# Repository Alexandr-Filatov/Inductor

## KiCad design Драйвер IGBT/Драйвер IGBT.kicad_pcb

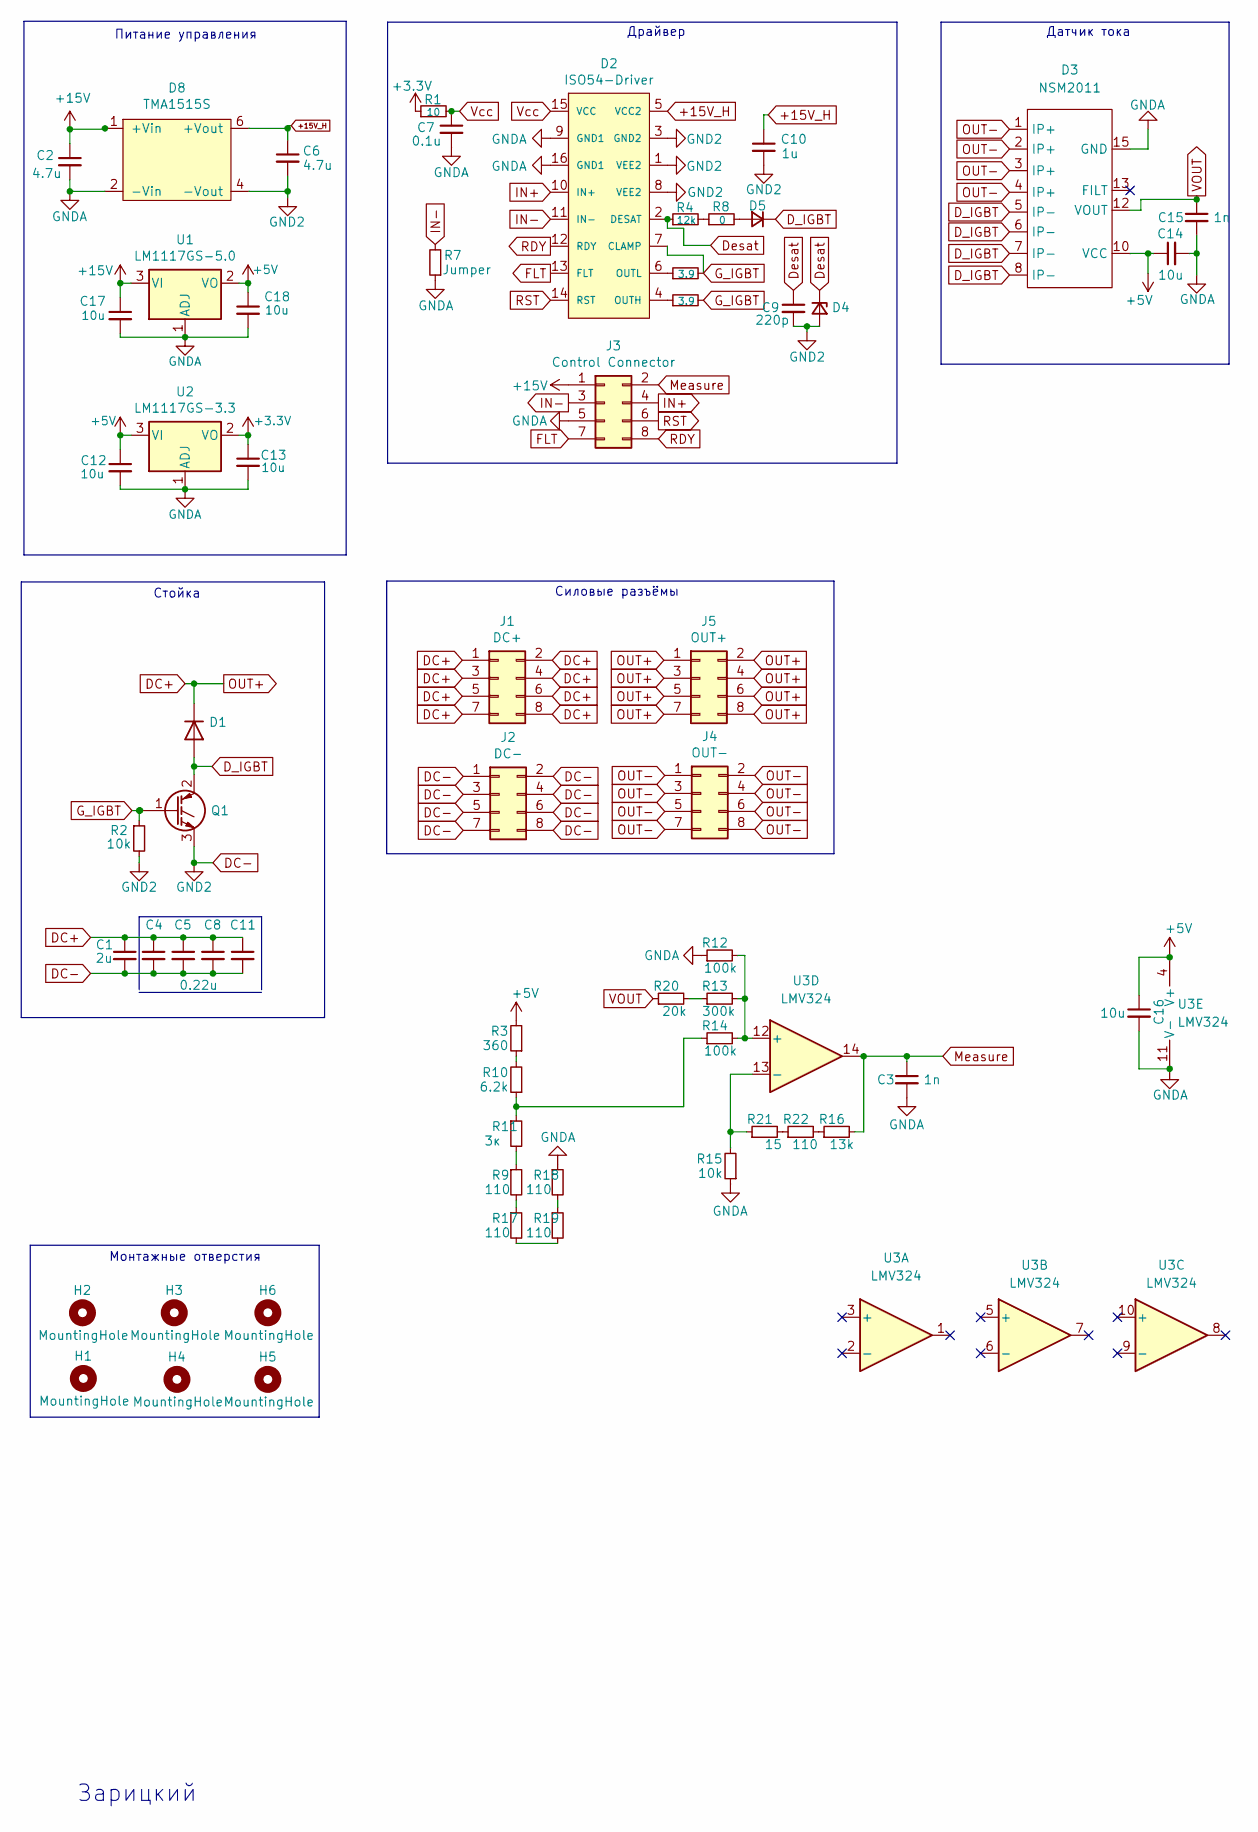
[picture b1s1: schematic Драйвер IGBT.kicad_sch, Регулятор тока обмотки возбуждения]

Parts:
C1: 2u; C_Rect_L31.5mm_W13.0mm_P27.50mm_MKS4
C2, C6: 4.7u; C_1210_3225Metric_Pad1.42x2.65mm_HandSolder
C3, C15: 1n; C_0805_2012Metric_Pad1.18x1.45mm_HandSolder
C4, C5, C8, C11: 0.22u; C_2220_5650Metric_Pad1.97x5.40mm_HandSolder
C7: 0.1u; C_0603_1608Metric_Pad1.05x0.95mm_HandSolder
C9: 220p; C_0603_1608Metric_Pad1.05x0.95mm_HandSolder
C10: 1u; C_0603_1608Metric_Pad1.05x0.95mm_HandSolder
C12, C13, C17, C18: 10u; C_0805_2012Metric_Pad1.15x1.40mm_HandSolder
C14, C16: 10u; C_0805_2012Metric_Pad1.18x1.45mm_HandSolder
D1: VS-60EPF06-M3; TO-247-2_Vertical
D2: ISO54-Driver; SOIC-16W_7.5x10.3mm_P1.27mm
D3: NSM2011; SOIC-16W_7.5x10.3mm_P1.27mm
D4: BZT52C10-7-F; D_SOD-123
D5: MURS360T3G; D_SMC
D8: TMA1515S
H1, H2, H3, H4, H5, H6: MountingHole; MountingHole_3mm
J1: DC+; Molex_Micro-Fit_3.0_43045-0800_2x04_P3.00mm_Horizontal
J2: DC-; Molex_Micro-Fit_3.0_43045-0800_2x04_P3.00mm_Horizontal
J3: Control Connector; Molex_Micro-Fit_3.0_43045-0800_2x04_P3.00mm_Horizontal
J4: OUT-; Molex_Micro-Fit_3.0_43045-0800_2x04_P3.00mm_Horizontal
J5: OUT+; Molex_Micro-Fit_3.0_43045-0800_2x04_P3.00mm_Horizontal
Q1: HGTG20N60A4; TO-247-3_Vertical
R1: 10; R_0805_2012Metric_Pad1.15x1.40mm_HandSolder
R2: 10k; R_0805_2012Metric_Pad1.15x1.40mm_HandSolder
R3: 360; R_0805_2012Metric_Pad1.20x1.40mm_HandSolder
R4: 12k; R_0805_2012Metric_Pad1.15x1.40mm_HandSolder
R5, R6: 3.9; R_1206_3216Metric_Pad1.42x1.75mm_HandSolder
R7: Jumper; R_0805_2012Metric_Pad1.15x1.40mm_HandSolder
R8: 0; D_SOD-123
R9, R17, R18, R19, R22: 110; R_0805_2012Metric_Pad1.20x1.40mm_HandSolder
R10: 6.2k; R_0805_2012Metric_Pad1.20x1.40mm_HandSolder
R11: 3к; R_0805_2012Metric_Pad1.20x1.40mm_HandSolder
R12, R14: 100k; R_0805_2012Metric_Pad1.20x1.40mm_HandSolder
R13: 300k; R_0805_2012Metric_Pad1.20x1.40mm_HandSolder
R15: 10k; R_0805_2012Metric_Pad1.20x1.40mm_HandSolder
R16: 13k; R_0805_2012Metric_Pad1.20x1.40mm_HandSolder
R20: 20k; R_0805_2012Metric_Pad1.20x1.40mm_HandSolder
R21: 15; R_0805_2012Metric_Pad1.20x1.40mm_HandSolder
U1: LM1117GS-5.0; SOT-223
U2: LM1117GS-3.3; SOT-223
U3: LMV324

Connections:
+3V3: C13.1, R1.1, U2.2 (VO)
+5V: C12.1, C14.1, C16.1, C18.1, D3.10 (VCC), R3.2, U1.2 (VO), U2.3 (VI), U3.4 (V+)
+15V: C2.1, C17.1, D8.1 (+Vin), J3.1, U1.3 (VI)
+15V_H: C6.1, C10.1, D2.5 (VCC2), D8.6 (+Vout)
DC+: C1.1, C4.1, C5.1, C8.1, C11.1, D1.1 (K), J1.1, J1.2, J1.3, J1.4, J1.5, J1.6, J1.7, J1.8, J5.1, J5.2, J5.3, J5.4, J5.5, J5.6, J5.7, J5.8
DC-: C1.2, C4.2, C5.2, C6.2, C8.2, C9.2, C10.2, C11.2, D2.1 (VEE2), D2.3 (GND2), D2.8 (VEE2), D4.2 (A), D8.4 (-Vout), J2.1, J2.2, J2.3, J2.4, J2.5, J2.6, J2.7, J2.8, Q1.3 (E), R2.2
D_IGBT: D1.2 (A), D3.5 (IP-), D3.6 (IP-), D3.7 (IP-), D3.8 (IP-), D5.1 (K), Q1.2 (C)
Desat: C9.1, D2.2 (DESAT), D4.1 (K), R4.1
FLT: D2.13 (FLT), J3.7
GNDA: C2.2, C3.2, C7.2, C12.2, C13.2, C14.2, C15.2, C16.2, C17.2, C18.2, D2.9 (GND1), D2.16 (GND1), D3.15 (GND), D8.2 (-Vin), J3.5, R7.1, R12.1, R15.1, R18.1, U1.1 (ADJ), U2.1 (ADJ), U3.11 (V-)
G_IGBT: D2.7 (CLAMP), Q1.1 (G), R2.1, R5.2, R6.2
IN+: D2.10 (IN+), J3.4
IN-: D2.11 (IN-), J3.3, R7.2
Measure: C3.1, J3.2, R16.2, U3.14
unnamed: D2.4 (OUTH), R6.1
unnamed: D2.6 (OUTL), R5.1
unnamed: D5.2 (A), R8.2
unnamed: R4.2, R8.1
unnamed: R3.1, R10.2
unnamed: R9.1, R11.2
unnamed: R12.2, R13.2, R14.2, U3.12 (+)
unnamed: R13.1, R20.2
unnamed: R10.1, R11.1, R14.1
unnamed: R15.2, R21.1, U3.13 (-)
unnamed: R16.1, R22.2
unnamed: R9.2, R17.1
unnamed: R17.2, R19.2
unnamed: R18.2, R19.1
unnamed: R21.2, R22.1
OUT-: D3.1 (IP+), D3.2 (IP+), D3.3 (IP+), D3.4 (IP+), J4.1, J4.2, J4.3, J4.4, J4.5, J4.6, J4.7, J4.8
RDY: D2.12 (RDY), J3.8
RST: D2.14 (RST), J3.6
VOUT: C15.1, D3.12 (VOUT), R20.1
Vcc: C7.1, D2.15 (VCC), R1.2

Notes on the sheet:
Драйвер
Зарицкий
Питание управления
Силовые разъёмы
Стойка
Монтажные отверстия
Датчик тока

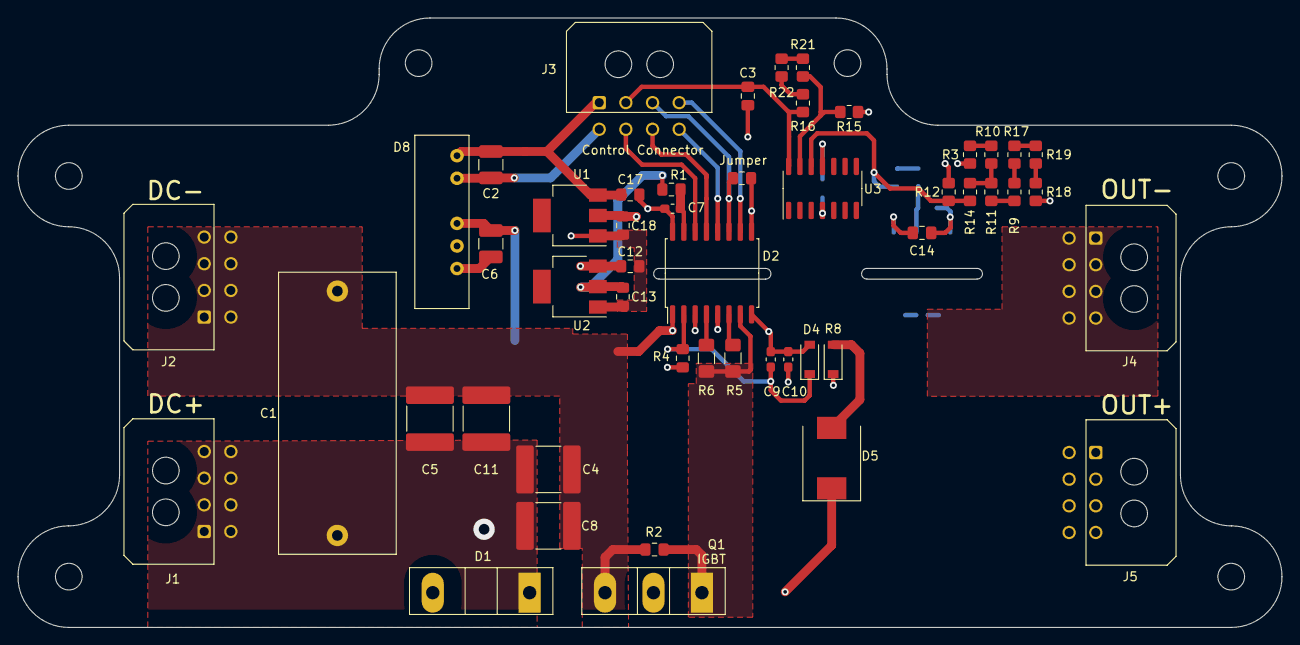
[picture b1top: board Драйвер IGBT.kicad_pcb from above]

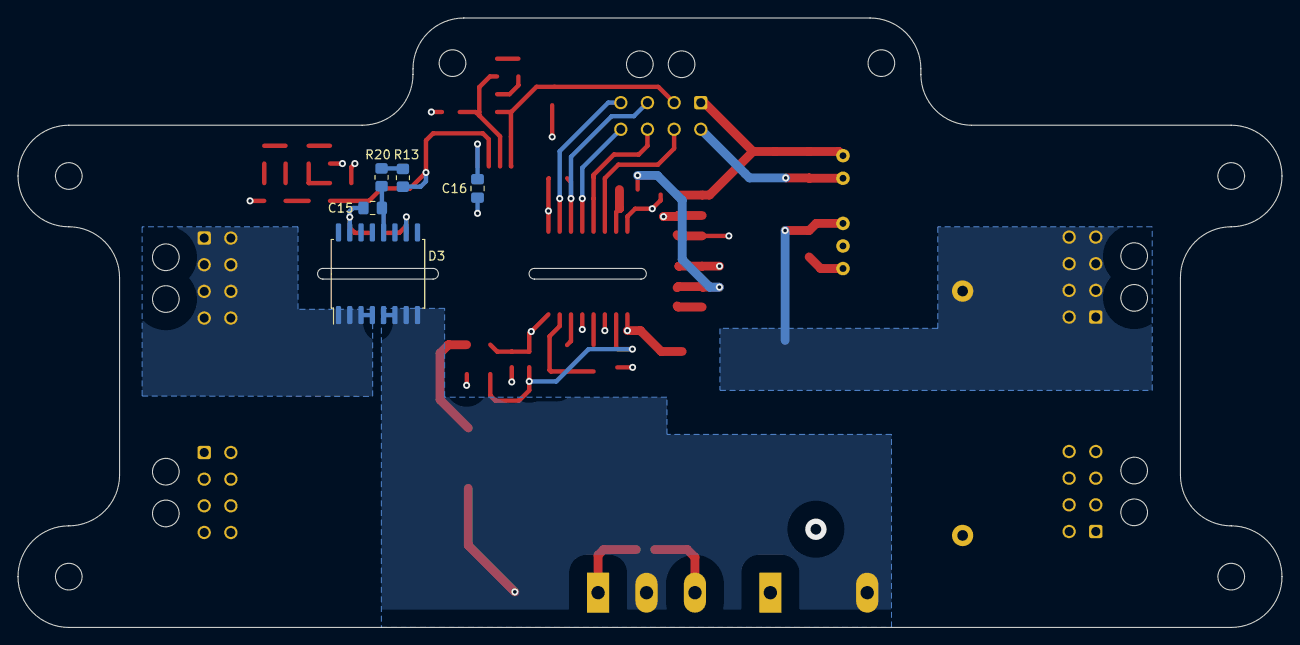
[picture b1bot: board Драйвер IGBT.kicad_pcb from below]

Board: 4 copper layers, 142.2 x 68.6 mm, 61 parts (5 on the bottom side), 34 nets.

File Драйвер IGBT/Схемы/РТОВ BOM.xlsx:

Item | Ref | Description | Package | Qty
1 | D2 | ISO5452 High-CMTI 2.5-A and 5-A Isolated IGBT | Package_SO:SOIC-16W_7.5x10.3mm_P1.27mm | 1
2 | C7 | 0.1uF 50V | Capacitor_SMD:C_0603_1608Metric_Pad1.05x0.95mm_HandSolder | 1
3 | C10 | 1uF 50V | Capacitor_SMD:C_0603_1608Metric_Pad1.05x0.95mm_HandSolder | 1
4 | C9 | 220pF 50V | Capacitor_SMD:C_0603_1608Metric_Pad1.05x0.95mm_HandSolder | 1
5 | R1 | 10 Ohm, 1% | Resistor_SMD:R_0805_2012Metric_Pad1.15x1.40mm_HandSolder | 1
6 | R5, R6 | 3.9 Ohm, 1% | Resistor_SMD:R_1206_3216Metric_Pad1.42x1.75mm_HandSolder | 2
7 | D4 | BZT52C10-7-F, Диод стабилитрон, 0,5Вт, 10В | Diode_SMD:D_SOD-123 | 1
8 | C2, C6 | 4.7uF 50V | Capacitor_SMD:C_1210_3225Metric_Pad1.42x2.65mm_HandSolder | 2
9 | C17, C18 | 10uF 50V | Capacitor_SMD:C_0805_2012Metric_Pad1.15x1.40mm_HandSolder | 2
10 | D6 | LPSR_50-NP | LPSR:LPSR_50 | 1
11 | R3 | 200 Ohm, 1% | Resistor_SMD:R_0805_2012Metric_Pad1.15x1.40mm_HandSolder | 1
12 | C3 | 10uF50V | Capacitor_SMD:C_0805_2012Metric_Pad1.15x1.40mm_HandSolder | 1
13 | R7 | 0 Ohm, 1% | Resistor_SMD:R_0805_2012Metric_Pad1.15x1.40mm_HandSolder | 1
14 | J1, J2, J3, J4, J5 | Гнездо, провод-плата MX-43045-0800 | Connector_Molex:Molex_Micro-Fit_3.0_43045-0800_2x04_P3.00mm_Horizontal | 5
15 | D5 | MURS360T3G | Diode_SMD:D_SMC | 1
16 | R8 | 0 Ohm, 1% Resistor | R_1206_3216Metric_Pad1.42x1.75mm_HandSolder | 1
17 | R4 | 12k Ohm | Resistor_SMD:R_0805_2012Metric_Pad1.15x1.40mm_HandSolder | 1
18 | U1 | LM1117GS-5.0 | Package_TO_SOT_SMD:SOT-223 | 1
19 | C12, C13 | 10uF 50V | Capacitor_SMD:C_0805_2012Metric_Pad1.15x1.40mm_HandSolder | 2
20 | U2 | LM1117GS-3.3 | Package_TO_SOT_SMD:SOT-223 | 1
21 | D1 | VS-60EPF06-M3 | Package_TO_SOT_THT:TO-247-2_Vertical | 1
22 | C4, C5, C8, C11 | 0.22uF 630V | Capacitor_SMD:C_2220_5650Metric_Pad1.97x5.40mm_HandSolder | 4
23 | C1 | 2uF 630V | Capacitor_THT:C_Rect_L31.5mm_W13.0mm_P27.50mm_MKS4 | 1
24 | R2 | 10k Ohm, 1% | Resistor_SMD:R_0805_2012Metric_Pad1.15x1.40mm_HandSolder | 1
25 | Q1 | HGTG20N60A4 | Package_TO_SOT_THT:TO-247-3_Vertical | 1
26 | D8 | TMA1515S | TRACO:TMA1515S | 1

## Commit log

2021-08-18 VER1.0
2021-08-18 VER2.0
2021-08-18 VER2.1
2021-08-18 VER2.2
2021-08-19 VER2.3
2021-09-30 VER2.4
2021-09-30 VER2.5
2023-02-17 VER2.6
